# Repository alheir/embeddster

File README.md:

# Embeddster: Plataforma de Pruebas para Sistemas Embebidos

- [Embeddster: Plataforma de Pruebas para Sistemas Embebidos](#embeddster-plataforma-de-pruebas-para-sistemas-embebidos)
  - [Descripción General](#descripción-general)
    - [¿Qué Hace Embeddster?](#qué-hace-embeddster)
  - [Características Principales](#características-principales)
    - [Hardware](#hardware)
    - [Firmware (ESP32)](#firmware-esp32)
    - [GUI (Python)](#gui-python)
  - [Uso sin GUI (Solo PCB + Terminal Serial)](#uso-sin-gui-solo-pcb--terminal-serial)
    - [Comandos Disponibles](#comandos-disponibles)
    - [Mensajes Recibidos (Formato Serial)](#mensajes-recibidos-formato-serial)
    - [Indicadores LED](#indicadores-led)
    - [Ejemplos de Uso](#ejemplos-de-uso)
      - [1. Monitorear tráfico CAN](#1-monitorear-tráfico-can)
      - [2. Generar tráfico CAN aleatorio](#2-generar-tráfico-can-aleatorio)
      - [3. Enviar mensaje CAN personalizado](#3-enviar-mensaje-can-personalizado)
      - [4. Controlar LED RGB de estación remota](#4-controlar-led-rgb-de-estación-remota)
      - [5. Cambiar modo CAN a Loopback (para pruebas sin bus)](#5-cambiar-modo-can-a-loopback-para-pruebas-sin-bus)
      - [6. Volver a modo Normal](#6-volver-a-modo-normal)
    - [Notas Importantes](#notas-importantes)
  - [Uso con GUI (Python)](#uso-con-gui-python)
    - [Instalación y Configuración](#instalación-y-configuración)
    - [Modo Normal](#modo-normal)
    - [CAN console](#can-console)
  - [Estructura del Proyecto](#estructura-del-proyecto)
  - [Protocolo de Comunicación](#protocolo-de-comunicación)
    - [Mensajes CAN (Formato)](#mensajes-can-formato)
      - [Ángulos (Angle Messages)](#ángulos-angle-messages)
      - [LEDs (LED Commands)](#leds-led-commands)
    - [Comandos Serial (ESP32 ↔ PC)](#comandos-serial-esp32--pc)
  - [Licencia](#licencia)
  - [Agradecimientos](#agradecimientos)

## Descripción General

**Embeddster** es una herramienta de desarrollo y pruebas para el curso **25.27 - Sistemas Embebidos** del ITBA (Instituto Tecnológico de Buenos Aires). Combina hardware (PCB con ESP32) y software (GUI en Python) para facilitar el desarrollo, depuración y evaluación de trabajos prácticos que involucran comunicación CAN, control de periféricos y protocolos embebidos.

### ¿Qué Hace Embeddster?
- **Hardware**: PCB personalizada que conecta un ESP32 a los periféricos de los TPs (encoder, displays 7-segmentos, LEDs, bus CAN).
- **Firmware**: Gestiona la comunicación serie con PC, controla LEDs de estado, maneja mensajes CAN (sniffer/envío) y soporta reintentos automáticos en caso de errores de bus.
- **GUI**: Aplicación Python con visualización 3D de estaciones, monitoreo de mensajes CAN, control de LEDs RGB y una CAN console para ver e inyectar tráfico.
  
---

## Características Principales

### Hardware
- **PCB Embeddster** (diseño en `hw/kicad/`):
  - Conecta ESP32 a encoder rotativo, displays 7-segmentos (via shift registers 74HC595), LED RGB (WS2812B), transceiver CAN (MCP2515), LEDs de estado.
  - Compatible con placa TP1 del curso (displays, encoder, LEDs de estado).

### Firmware (ESP32)
- **Ubicación**: `fw/` (proyecto PlatformIO).
- **Funcionalidades**:
  - **Modos de operación**: Sniffer CAN (M1) y Random Send (M2), cambiables por comandos seriales.
  - **Protocolo serial**: Comandos para cambiar modos CAN (NORMAL/LOOPBACK), enviar mensajes CAN personalizados y controlar LEDs RGB.
  - **Reintentos automáticos**: Si falla el envío de un mensaje CAN (por error de bus), entra en "Retry Mode" (LED amarillo encendido) e intenta reenviarlo cada 2 segundos.
  - **Indicadores visuales**: LEDs de colores para estado del sistema (azul=sniffer, verde=random send, amarillo=retry, blanco=loopback).

### GUI (Python)
- **Ubicación**: `gui/` (PyQt6, OpenGL, Matplotlib).
- **Funcionalidades**:
  - **Visualización 3D**: Modelos de estaciones con orientación en tiempo real (roll/pitch/yaw).
  - **Control de LEDs**: Envío de comandos RGB a estaciones específicas.
  - **CAN console**: Monitoreo CAN, inyección de mensajes, filtros por ID, logs y export.
  - **Soporte TP2**: Extensión de [TiltNetworkTool](https://github.com/alheir/TiltNetworkTool), basado en [canmon](https://github.com/alheir/canmon).

## Uso sin GUI (Solo PCB + Terminal Serial)

En este modo, el ESP32 funciona de manera autónoma. Conecta un terminal serial a 115200 baud, 8N1. El ESP32 **inicia automáticamente en modo Sniffer (LED azul)**.

### Comandos Disponibles

| Comando | Descripción | Ejemplo |
|---------|-------------|---------|
| `M1` | Cambiar a **Sniffer Mode** (azul). Escucha mensajes CAN y los reenvía por serial. | `M1\n` |
| `M2` | Cambiar a **Random Send Mode** (verde). Genera y envía mensajes CAN aleatorios (ángulos simulados). | `M2\n` |
| `MODE_NORMAL` | Configurar controlador CAN en modo **Normal** (comunicación estándar). LED blanco OFF. | `MODE_NORMAL\n` |
| `MODE_LOOPBACK` | Configurar controlador CAN en modo **Loopback** (pruebas sin bus externo). LED blanco ON. | `MODE_LOOPBACK\n` |
| `SEND_{id}_{b1}_{b2}_...` | Enviar mensaje CAN personalizado. `{id}` en hex, `{b1}...` bytes en hex. | `SEND_100_52_2D_31_30\n` |
| `LED_{station}_{r}_{g}_{b}` | Controlar LED RGB de una estación. `{r/g/b}` = 0 o 1. | `LED_0_1_0_0\n` (estación 0, rojo ON) |

### Mensajes Recibidos (Formato Serial)

**En Modo Sniffer (M1)**:
```
RXED: ID=0x100 Data=0x522D3130='R-10' Len=4
RXED: ID=0x101 Data=0x432B3532='C+52' Len=4
```

**En Modo Random Send (M2)**:
```
SENT ANGLE: ID=0x100 Data=0x522D3134='R-14' Len=5
SENT ANGLE: ID=0x100 Data=0x432B3837='C+87' Len=5
```

**En Retry Mode** (si falla envío):
```
Error sending CAN msg: R-10

~~~~ ENTERING RETRY MODE ~~~~
Failed message: ID=0x100 Data='R-10'
RETRY: Attempting to resend ID=0x100 Data='R-10'
RETRY: Failed, will retry again...
```

### Indicadores LED

| LED | Color | Significado |
|-----|-------|-------------|
| D5 | Azul | Modo Sniffer activo |
| D6 | Verde | Modo Random Send activo |
| D4 | Amarillo | Retry Mode (reintentando envío fallido) |
| D3 | Blanco | Modo Loopback del controlador CAN activo |

### Ejemplos de Uso

#### 1. Monitorear tráfico CAN
```bash
# El ESP32 ya inicia en sniffer, pero si cambias de modo, vuelve con:
M1

# Verás mensajes como:
# RXED: ID=0x100 Data=0x522D3130='R-10' Len=4
```

#### 2. Generar tráfico CAN aleatorio
```bash
M2

# El ESP32 enviará mensajes aleatorios con diferentes formatos:
# SENT ANGLE: ID=0x100 Data=0x522D3134='R-14' Len=4    # Formato simple
# SENT ANGLE: ID=0x101 Data=0x432B3435='C+45' Len=4    # Con signo explícito
# SENT ANGLE: ID=0x102 Data=0x4F3030='O00' Len=3       # Zero-padded 2 dígitos
# SENT ANGLE: ID=0x100 Data=0x522D303732='R-072' Len=5 # Zero-padded 3 dígitos
# SENT ANGLE: ID=0x101 Data=0x432B313037='C+107' Len=6 # Signo + padding
```

**Características del Random Send**:
- Simula **4 estaciones** (IDs 0x100-0x103) con tráfico aleatorio.
- Genera mensajes en **6 formatos diferentes** para probar robustez del parser:
  - Simple: `'R-34'`, `'C0'`, `'O67'` (sin signo para positivos, sin padding)
  - Signo explícito: `'R+138'`, `'C+5'` (siempre muestra +/-)
  - Zero-padded 2 dígitos: `'R00'`, `'C-07'`
  - Zero-padded 3 dígitos: `'O000'`, `'C-072'`
  - Signo + padding: `'R+107'`, `'C+045'`
  - Mixto (aleatorio entre formatos)
- Intervalos aleatorios entre **100ms y 2 segundos** entre mensajes.
- Valores varían en hasta ±30° del anterior, limitados a -179° a 180°.

#### 3. Enviar mensaje CAN personalizado
```bash
# Enviar a ID 0x105: bytes 0x41 0x42 0x43 ('ABC')
SEND_105_41_42_43

# Respuesta:
# SEND: ID=0x105 Data=0x414243='ABC' Len=3 - SUCCESS

# Si falla (e.g., bus desconectado):
# SEND: ID=0x105 Data=0x414243='ABC' Len=3 - ERROR
```

#### 4. Controlar LED RGB de estación remota
```bash
# Estación 1, LED verde encendido (r=0, g=1, b=0)
LED_1_0_1_0

# Respuestao:
# LED CMD: Station=1 RGB=(0,1,0) - LED command sent via CAN

# Si es estación propia (GROUP_NUMBER=0):
# LED CMD: Station=0 RGB=(1,0,0) - Own LED updated

# Si falla el envío remoto:
# LED CMD: Station=1 RGB=(0,1,0) - ERROR sending CAN
```

#### 5. Cambiar modo CAN a Loopback (para pruebas sin bus)
```bash
MODE_LOOPBACK

# Respuesta:
# CAN mode set to LOOPBACK
# LED blanco se enciende
```

#### 6. Volver a modo Normal
```bash
MODE_NORMAL

# Respuesta:
# CAN mode set to NORMAL
# LED blanco se apaga
```

### Notas Importantes
- **Retry Mode**: Si el bus CAN está desconectado o hay errores, el ESP32 entra en modo retry (LED amarillo). Intentará reenviar el mensaje fallido cada 2 segundos hasta que tenga éxito o cambies de modo.
- **Comandos ignorados**: Si envías `M1` estando ya en sniffer, no hace nada. Lo mismo para `M2` en random send.
- **Formato de datos**: Los mensajes CAN usan formato ASCII para ángulos (e.g., `R-10` = Roll -10 grados). LEDs usan formato binario empaquetado (ver código en `main.cpp`).

---

## Uso con GUI (Python)

La GUI proporciona una interfaz visual para interactuar con las estaciones CAN, monitorear mensajes en tiempo real y controlar LEDs.

### Instalación y Configuración

Requiere **Python 3.11 o 3.12**.

**Con uv (recomendado):**

```bash
cd gui
uv sync
uv run python main.py
```

**Sin uv (alternativa):**

1. Crear entorno virtual en `gui/`:
   ```bash
   cd gui
   python -m venv .venv
   ```

2. Activar el entorno virtual:
   - Windows: `.venv\Scripts\activate`
   - Linux/Mac: `source .venv/bin/activate`

3. Instalar dependencias:
   ```bash
   pip install -r requirements.txt
   ```

4. Ejecutar la aplicación:
   ```bash
   python main.py
   ```

### Modo Normal

**Características**:
- **Visualización 3D**: Modelos de estaciones (FRDM-K64F o avión) con orientación en tiempo real basada en mensajes CAN (Roll/Pitch/Yaw).
- **Panel de estaciones**: Muestra últimos valores de ángulos, tiempo desde última actualización y botón para gráficos históricos.
- **Control de LEDs**: Selecciona estación y colores RGB para enviar comandos LED via CAN.
- **Emulador**: Modo simulación sin hardware real (opción "Serial Data Emulator" en selector de puertos).

**Cómo usar**:
1. Conecta el ESP32 por USB.
2. Selecciona el puerto COM en la GUI y haz clic en "Connect".
3. Los mensajes CAN se procesarán automáticamente (via [`ProtocolHandler`](gui/src/protocol/protocol_handler.py)).
4. Para enviar LED: Selecciona estación, marca colores (R/G/B) y haz clic en "Send LED Command".

### CAN console

**Acceso**: Menú "Actions" → "CAN console" (requiere conexión real, no emulador).

**Características**:
- **Control de modos CAN**: Cambiar entre Normal y Loopback directamente desde la interfaz.
- **Monitoreo CAN**: Tabla con timestamp, ID, DLC, tipo (Angle/LED/Unknown), datos en hex y ASCII/binario.
- **Inyección de mensajes**:
  - **Manual**: Enviar mensajes CAN con ID y datos personalizados (hex o ASCII).
  - **Angle Message**: Enviar ángulos a múltiples grupos simultáneamente (selección con checkboxes).
  - **LED Command**: Controlar LEDs RGB de estaciones remotas.
  - **Random Traffic**: Generar tráfico CAN aleatorio con modos configurables por grupo (Sine/Const/Noise).
- **Filtros**: Filtrar mensajes por IDs específicos.
- **Logs detallados**: Panel inferior con historial de mensajes (exportable a TXT).
- **Tabla de estaciones**: Estado de última recepción de Roll/Pitch/Yaw con timestamps.

**Comportamiento especial**:
- Al abrir la CAN console, el ESP32 se pone automáticamente en **modo Sniffer (M1)**.
- Al cerrar la CAN console o la aplicación, el ESP32 se resetea a **modo Normal y Sniffer**.

**Ejemplo de uso**:
1. Abre CAN console desde el menú.
2. Para inyectar un ángulo: modo "Angle", grupos, tipo, valor, "Send".
3. Para modo Loopback: Haz clic en "Loopback". El LED blanco en la placa se encenderá.
4. Para filtrar: marca "Filter" e ingresa IDs separados por coma (`0x100, 0x101`).

---

## Estructura del Proyecto

```
embeddster/
├── fw/                    # Firmware ESP32 (PlatformIO)
│   ├── src/main.cpp       # Lógica principal (sniffer, random send, retry)
│   ├── include/           # Headers (pin_assignment, tp1board, sr595)
│   └── platformio.ini     # Configuración de compilación
├── gui/                   # GUI Python (PyQt6)
│   ├── main.py            # Punto de entrada
│   ├── src/
│   │   ├── mainwindow.py  # Ventana principal
│   │   ├── protocol/      # ProtocolHandler para parseo de mensajes
│   │   └── widgets/       # CAN console, plots, visualizador 3D
│   ├── pyproject.toml     # Dependencias y config (uv/ruff)
│   ├── uv.lock            # Versiones fijadas (uv)
│   └── requirements.txt   # Export para pip (generado)
├── hw/                    # Diseño PCB (KiCad)
│   └── kicad/             # Esquemáticos y layout
├── docs/                  # Imágenes para README
└── README.md              # Este archivo
```

---

## Protocolo de Comunicación

### Mensajes CAN (Formato)

#### Ángulos (Angle Messages)
- **ID**: `0x100 + {station_number}` (e.g., estación 0 = 0x100, estación 1 = 0x101).
- **Datos**: ASCII `{tipo}{valor}` en formato variable (1-6 bytes):
  - `{tipo}`: `'R'` (Roll), `'C'` (Pitch/Cabeceo), `'O'` (Yaw/Orientación)
  - `{valor}`: Ángulo entre -179° y 180° en diferentes formatos válidos:
    - **Simple**: `'R-10'`, `'C0'`, `'O67'` (sin signo para positivos)
    - **Signo explícito**: `'R+138'`, `'C+5'` (con + o -)
    - **Zero-padded**: `'R00'`, `'C-072'`, `'O000'` (2 o 3 dígitos)
    - **Combinado**: `'R+107'`, `'C+045'` (signo + padding)
  - **Ejemplos válidos**: `'R-34'`, `'C0'`, `'O67'`, `'R+138'`, `'R00'`, `'C-072'`, `'R+107'`, `'O000'`
  - Longitud variable (DLC 2-5 bytes típicamente).

#### LEDs (LED Commands)
- **ID**: Mismo que ángulos (`0x100 + station`).
- **Datos**: 1 byte en formato `1JKL 0RGB`:
  - Bit 7: Siempre 1 (identificador LED).
  - Bits 6-4 (JKL): Número de estación destino.
  - Bits 2-0 (RGB): Estados de colores (1=encendido, 0=apagado).

### Comandos Serial (ESP32 ↔ PC)

Ver tabla en sección "Uso sin GUI" para lista completa.

## Licencia

Licencia MIT (ver [`LICENSE`](LICENSE)).

---

## Agradecimientos

- **Cátedra de Sistemas Embebidos (ITBA)**: Daniel Andrés Jacoby, Nicolás Magliola y Matías Bergerman por las especificaciones de TPs y soporte.
- **Proyectos relacionados**: [TiltNetworkTool](https://github.com/alheir/TiltNetworkTool) (base GUI, diseñado originalmente por el Ing. Juan Francisco Sbruzzi) y [canmon](https://github.com/alheir/canmon).

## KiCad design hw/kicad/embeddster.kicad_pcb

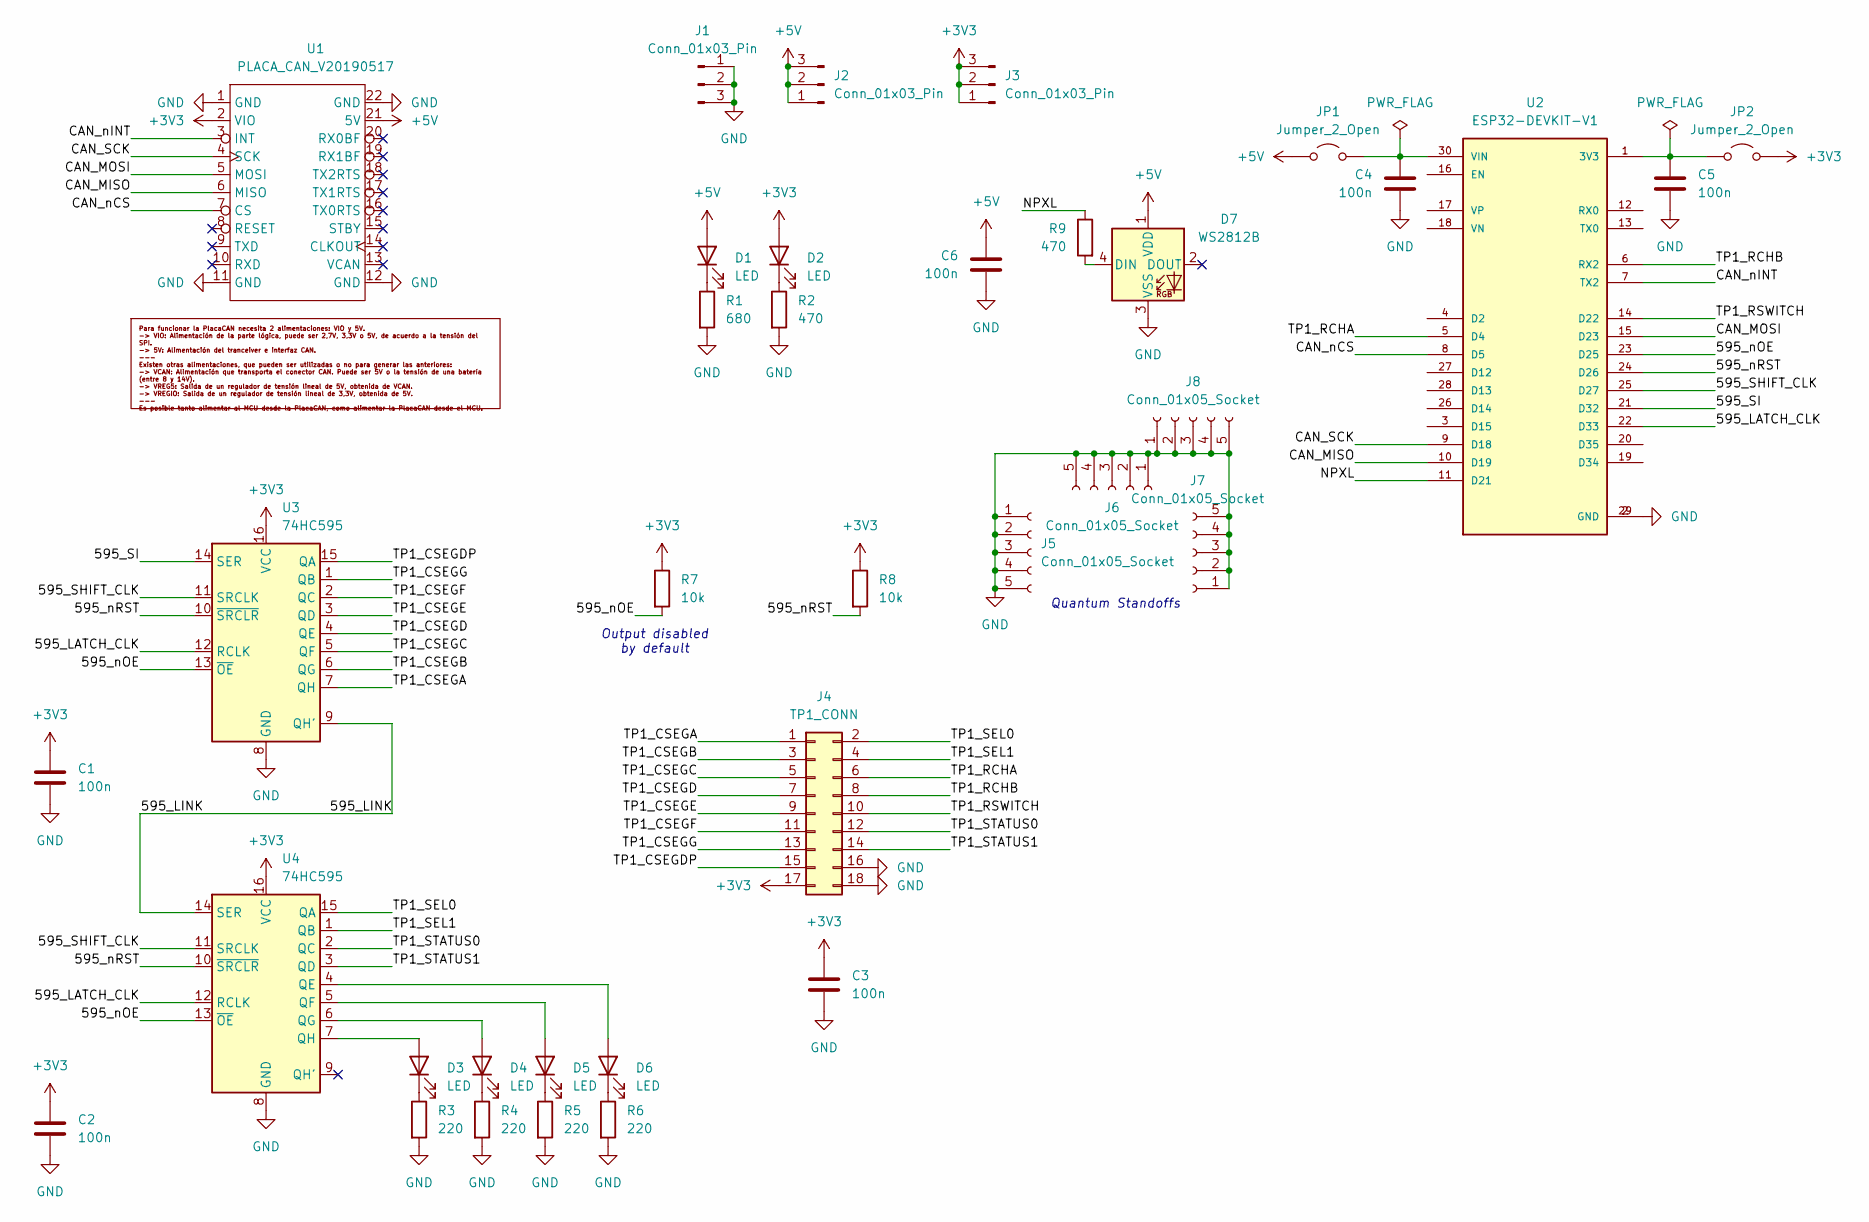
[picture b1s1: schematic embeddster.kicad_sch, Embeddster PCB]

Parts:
C1, C2, C3, C4, C5, C6: 100n; C_0805_2012Metric_Pad1.18x1.45mm_HandSolder
D1: LED; LED_D3.0mm
D2, D3, D4, D5, D6: LED; LED_0805_2012Metric_Pad1.15x1.40mm_HandSolder
D7: WS2812B; LED_WS2812B_PLCC4_5.0x5.0mm_P3.2mm
J1, J2, J3: Conn_01x03_Pin; PinHeader_1x03_P2.54mm_Vertical
J4: TP1_CONN; PinSocket_2x09_P2.54mm_Vertical
J5, J6, J7, J8: Conn_01x05_Socket; PinSocket_1x05_P2.54mm_Vertical
JP1, JP2: Jumper_2_Open; TestPoint_2Pads_Pitch2.54mm_Drill0.8mm
R1: 680; R_0805_2012Metric_Pad1.20x1.40mm_HandSolder
R2, R9: 470; R_0805_2012Metric_Pad1.20x1.40mm_HandSolder
R3, R4, R5, R6: 220; R_0805_2012Metric_Pad1.20x1.40mm_HandSolder
R7, R8: 10k; R_0805_2012Metric_Pad1.20x1.40mm_HandSolder
U1: PLACA_CAN_V20190517
U2: ESP32-DEVKIT-V1; MODULE_ESP32_DEVKIT_V1; PARTREV N/A
U3, U4: 74HC595; SOIC-16_3.9x9.9mm_P1.27mm

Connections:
+3V3: C1.2, C2.2, C3.2, D2.2 (A), J3.1, J3.2, J3.3, J4.17, JP2.2 (B), R7.1, R8.1, U1.2 (VIO), U3.16 (VCC), U4.16 (VCC)
+5V: C6.2, D1.2 (A), D7.1 (VDD), J2.1, J2.2, J2.3, JP1.1 (A), U1.21 (5V)
/595_LATCH_CLK: U2.22 (D33), U3.12 (RCLK), U4.12 (RCLK)
/595_LINK: U3.9 (QH'), U4.14 (SER)
/595_SHIFT_CLK: U2.25 (D27), U3.11 (SRCLK), U4.11 (SRCLK)
/595_SI: U2.21 (D32), U3.14 (SER)
/595_nOE: R7.2, U2.23 (D25), U3.13 (~OE), U4.13 (~OE)
/595_nRST: R8.2, U2.24 (D26), U3.10 (~SRCLR), U4.10 (~SRCLR)
/CAN_MISO: U1.6 (MISO), U2.10 (D19)
/CAN_MOSI: U1.5 (MOSI), U2.15 (D23)
/CAN_SCK: U1.4 (SCK), U2.9 (D18)
/CAN_nCS: U1.7 (CS), U2.8 (D5)
/CAN_nINT: U1.3 (INT), U2.7 (TX2)
/NPXL: R9.1, U2.11 (D21)
/TP1_CSEGA: J4.1, U3.7 (QH)
/TP1_CSEGB: J4.3, U3.6 (QG)
/TP1_CSEGC: J4.5, U3.5 (QF)
/TP1_CSEGD: J4.7, U3.4 (QE)
/TP1_CSEGDP: J4.15, U3.15 (QA)
/TP1_CSEGE: J4.9, U3.3 (QD)
/TP1_CSEGF: J4.11, U3.2 (QC)
/TP1_CSEGG: J4.13, U3.1 (QB)
/TP1_RCHA: J4.6, U2.5 (D4)
/TP1_RCHB: J4.8, U2.6 (RX2)
/TP1_RSWITCH: J4.10, U2.14 (D22)
/TP1_SEL0: J4.2, U4.15 (QA)
/TP1_SEL1: J4.4, U4.1 (QB)
/TP1_STATUS0: J4.12, U4.2 (QC)
/TP1_STATUS1: J4.14, U4.3 (QD)
GND: C1.1, C2.1, C3.1, C4.1, C5.1, C6.1, D7.3 (VSS), J1.1, J1.2, J1.3, J4.16, J4.18, J5.1, J5.2, J5.3, J5.4, J5.5, J6.1, J6.2, J6.3, J6.4, J6.5, J7.1, J7.2, J7.3, J7.4, J7.5, J8.1, J8.2, J8.3, J8.4, J8.5, R1.2, R2.2, R3.2, R4.2, R5.2, R6.2, U1.1 (GND), U1.11 (GND), U1.12 (GND), U1.22 (GND), U2.2 (GND), U2.29 (GND), U3.8 (GND), U4.8 (GND)
unnamed: D1.1 (K), R1.1
unnamed: D2.1 (K), R2.1
unnamed: D3.2 (A), U4.7 (QH)
unnamed: D3.1 (K), R3.1
unnamed: D4.2 (A), U4.6 (QG)
unnamed: D4.1 (K), R4.1
unnamed: D5.2 (A), U4.5 (QF)
unnamed: D5.1 (K), R5.1
unnamed: D6.2 (A), U4.4 (QE)
unnamed: D6.1 (K), R6.1
unnamed: D7.4 (DIN), R9.2
unnamed: C4.2, JP1.2 (B), U2.30 (VIN)
unnamed: C5.2, JP2.1 (A), U2.1 (3V3)

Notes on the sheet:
Output disabled by default
Quantum Standoffs

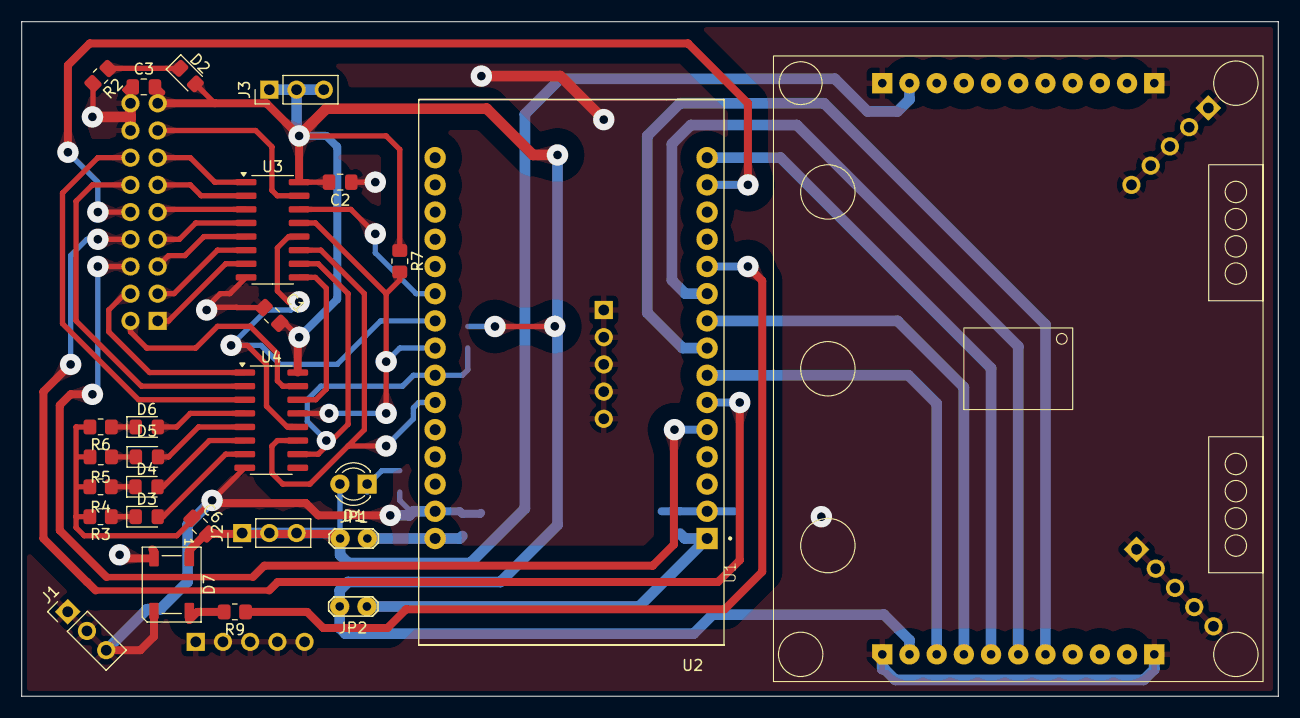
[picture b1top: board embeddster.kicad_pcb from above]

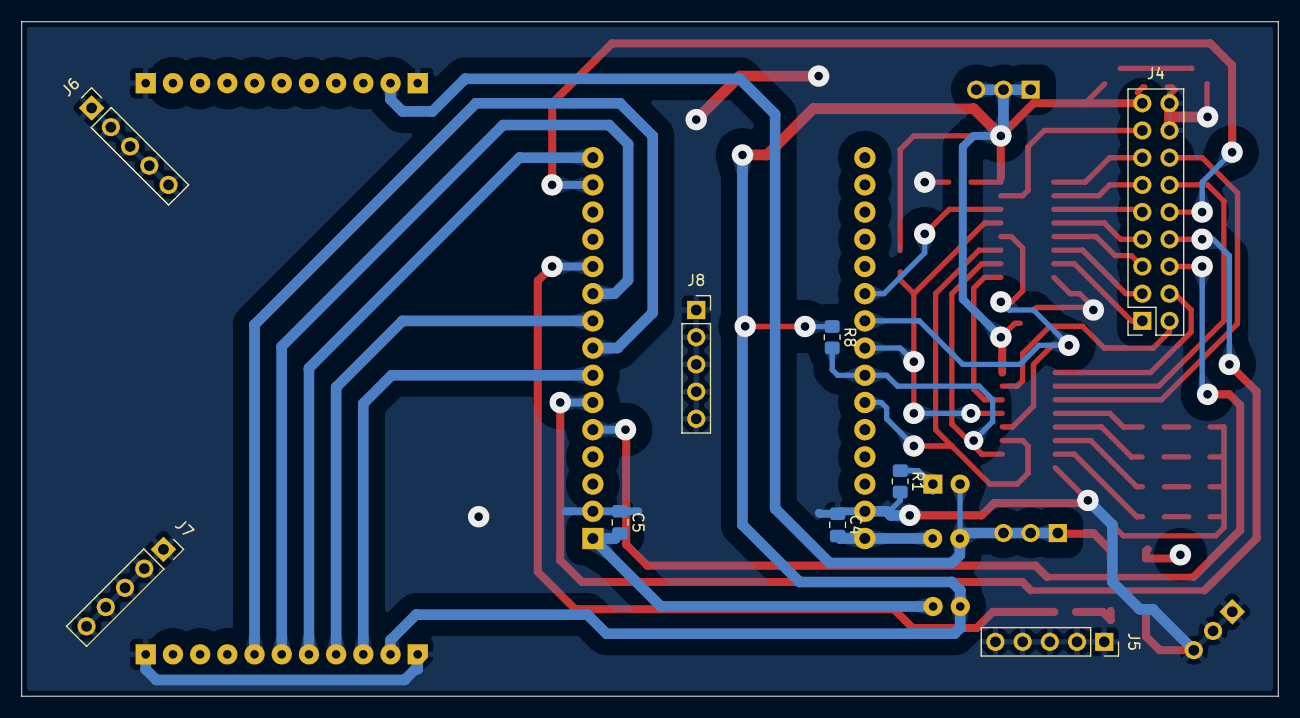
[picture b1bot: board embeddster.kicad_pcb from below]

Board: 2 copper layers, 117.3 x 63.0 mm, 36 parts (9 on the bottom side), 43 nets.

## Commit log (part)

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2025-09-13 Add initial KiCad project and library files for ESP32-DEVKIT-V1
2025-09-13 Add initial GUI files including .gitignore, requirements, and empty main script
2025-09-13 Add initial firmware structure (PlatformIO) with configuration and source files
2025-09-13 Add README.md with project overview and key features
2025-09-18 Add custom KiCad symbol&footproint for PLACA_CAN_V20190517
2025-09-18 Add 3D models for PLACA_CAN_V20190517 connector pins
2025-09-18 Remove mounting holes from ESP32 footprint
2025-09-18 sch supporting tp1 & tp2
2025-09-18 Remove unnecessary zone definitions from ESP32 DevKit V1 footprint
2025-09-18 Add 3D models for ESP32 DevKit V1 connector pins
2025-09-18 pcb ready for fab
2025-09-18 Add pin assignment header for MCP, encoder, and 74HC595 control, based on PCB
2025-09-20 Add 4th quantum standoff to PCB, ground plane adjustments
2025-09-22 Add a WS2812B cell
2025-09-22 Add active low definition for encoder switch
2025-09-22 Update README to remove TP3 reference and clarify hardware interface
2025-09-26 Fix routing, remove old pic
2025-09-26 re-fix routing
2025-09-26 Pcb v0 (#1)
    * Add custom KiCad symbol&footproint for PLACA_CAN_V20190517
    * Add 3D models for PLACA_CAN_V20190517 connector pins
    * Remove mounting holes from ESP32 footprint
    * sch supporting tp1 & tp2
    * Remove unnecessary zone definitions from ESP32 DevKit V1 footprint
    * Add 3D models for ESP32 DevKit V1 connector pins
2025-09-26 Add pin assignment header file with definitions for MCP, WS2812B, encoder, and 74HC595 control pins
2025-09-26 Add library dependencies for SPI, MCP_CAN, and Adafruit NeoPixel
2025-09-26 Refactor main.cpp to initialize NeoPixel and MCP/CAN in setup function
2025-09-26 Implement SR595 class for controlling 74HC595 shift registers and integrate into main setup
2025-09-26 Add initial TP1BOARD class for managing display and encoder functionality
2025-10-04 Add TiltNetworkTool v1.0.0 as base GUI
2025-10-06 Update LED pin definitions for clarity and consistency
2025-10-06 Refactor SR595 reset method to include latch option and update TP1BOARD to use new functionality
2025-10-06 Update MCP/CAN initialization to use 16MHz clock
2025-10-06 Implement CAN sniffer and random send functionality
2025-10-08 Restore initialize TP1BOARD in setup; accidentally removed
2025-10-08 Refactor setup function to improve readability and consistency; replace hardcoded delays with SETUP_DELAY_MS and enhance serial output formatting
2025-10-08 Add LED toggle functionality in CAN sniffer and random send methods
2025-10-10 Add 'God mode' action to the main menu with custom font settings
2025-10-10 Add God Mode widget for advanced CAN monitoring and message injection
2025-10-10 Refactor random traffic message logging and error handling in GodModeWidget
2025-10-10 Refactor layout of GodModeWidget for improved organization and readability
2025-10-10 Close God Mode widget on main window close event
2025-10-11 Refactor setup and loop functions to remove button handling and improve serial command processing for mode switching
2025-10-11 Refactor FrdmViewerWidget to use dynamic paths for model and shader files
2025-10-11 Refactor GodModeWidget to use STATION_COUNT for dynamic station handling
2025-10-11 Refactor GodModeWidget to improve code readability
2025-10-11 Add connection check before opening God Mode widget
2025-10-11 Implement ProtocolHandler and main.cpp for integrating fw and gui, supporting God Mode or default GUI
2025-10-11 Refactor command handling to simplify mode switching and ensure M1 command is sent on serial disconnect and God Mode activation
2025-10-11 Refactor message processing to streamline forwarding to God Mode and normal processing
2025-10-11 Fix parsing of CAN messages to correctly extract ASCII data and handle positive/negative values
2025-10-11 Enhance CAN message handling to support LED commands and improve angle message parsing
2025-10-11 Update CAN message display to include message type and adjust table headers
2025-10-11 Add LED state handling and update UI in StationInfoWidget
2025-10-11 Refactor CAN message handling to process messages as dictionaries and improve angle message parsing
2025-10-11 Add group selection for angle messages and update sending logic
2025-10-11 Implement LED control methods and enhance initialization sequence for visual feedback
2025-10-11 Update refresh interval and use white LED to indicate LOOPBACK mode
2025-10-11 Update CAN message display to include binary format for LED data
2025-10-11 Replace NPXL with discrete LEDs for indicating sniffer or random send mode.
2025-10-11 Add refresh call after setup completion for LED state update
2025-10-11 Update README.md with detailed usage instructions and add GUI images
2025-10-11 Feat/gui-n-fw-integration (#4)
    * Implement ProtocolHandler and main.cpp for integrating fw and gui, supporting God Mode or default GUI
    * Refactor command handling to simplify mode switching and ensure M1 command is sent on serial disconnect and God Mode activation
    * Refactor message processing to streamline forwarding to God Mode and normal processing
    * Fix parsing of CAN messages to correctly extract ASCII data and handle positive/negative values
    * Enhance CAN message handling to support LED commands and improve angle message parsing
    * Update CAN message display to include message type and adjust table headers
2025-10-12 Implement retry mechanism for CAN message sending and enhance LED feedback
2025-10-12 Refactor main.cpp to improve structure and readability
2025-10-12 Update README.md to enhance structure, add detailed usage instructions, and clarify features of the Embeddster platform
2025-10-12 Refactor random send logic to use dynamic station selection and improve angle value handling
2025-10-12 Enhance random angle message generation with multiple formats and improved value handling
2025-10-12 Add main README pdf
2025-10-12 Enhance CAN message logging and LED command feedback in firmware
2025-10-13 Add PCB top reference image to documentation
2025-10-13 Initial plan
2025-10-13 Add DeepWiki badge to main README
2025-10-13 Add LED command handling to CAN sniffer
2025-10-13 Re-format main.cpp
2025-10-13 Feat/handle-rxed-led-can-msgs (#7)
    * Add LED command handling to CAN sniffer
    * Re-format main.cpp
